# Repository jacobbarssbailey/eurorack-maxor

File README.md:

# MaxOr

There are a number of commercial eurorack-format synthesizer modules available that will work as a logical OR function. While they do a fine job combining multiple gate/trigger signals, typically they work by passing each input through a diode, resulting in the output being the maximum input level minus the the voltage drop across the diodes. Fine for gates and triggers, not so fine for combining control voltages.

This module takes a similar approach to these passive modules, but exchanges the passive diodes for "ideal" diodes (i.e. an opamp and two diodes that conspire to behave like normal diodes, only with a magical 0V voltage drop). The result is a module that precisely combines multiple CVs, and outputs the maximum value from the set.

### Why would you want this?

* Combine several envelopes in a new way
* Combine gate / trigger signals without losing 1V-2V in the process
* Use a constant voltage source to set a lower bound on another CV
* Something else!

## Behavior

Each channel accepts three inputs, and the maximum (positive) voltage among them becomes the output. Some examples of what you should expect:

| Input A | Input B | Input C | Output |
| ------- | ------- | ------- | ------ |
|      0V |      0V |      1V |     1V |
|      1V |      3V |      2V |     3V |
|      5V |      0V |      5V |     5V |
|      5V |      8V |      5V |     8V |
|     -5V |     -8V |      0V |     0V |
|     -8V |     -3V |     -2V |     0V |

Note that this module does nothing for negative voltages; they are treated as if they were 0V. For this reason alone, I don't recommend using this module for audio signals.

## Construction

This module is designed to be milled from a single singled PCB, on an Othermill, though it should also be relatively easy to etch by hand. As such, I've favored hand-solderable surface mount components, to limit the amount of through-hole drilling, and kept all trace gaps to no less than 1/64". The board design could probably be better optimized, before being sent to a commercial board manufacturer, but for home milling, it works quite well.

Jacks are Erthenvar horizontal jacks. At time of writing, they come in packs of 50, and have nice heavy solder tabs.

Pads for protection diodes are included, but to use these, you'll need to cut /remove the traces across them. I included them and then didn't bother with them, in favor of a keyed power connector.

There are no extra power smoothing capacitors on this module, just some 100nF decoupling capacitors around the op amps. If your power distribution board doesn't already contain a few 100µF capacitors nearby, you might find this module oscillating.

Total module depth is about 1.7" (~44mm).

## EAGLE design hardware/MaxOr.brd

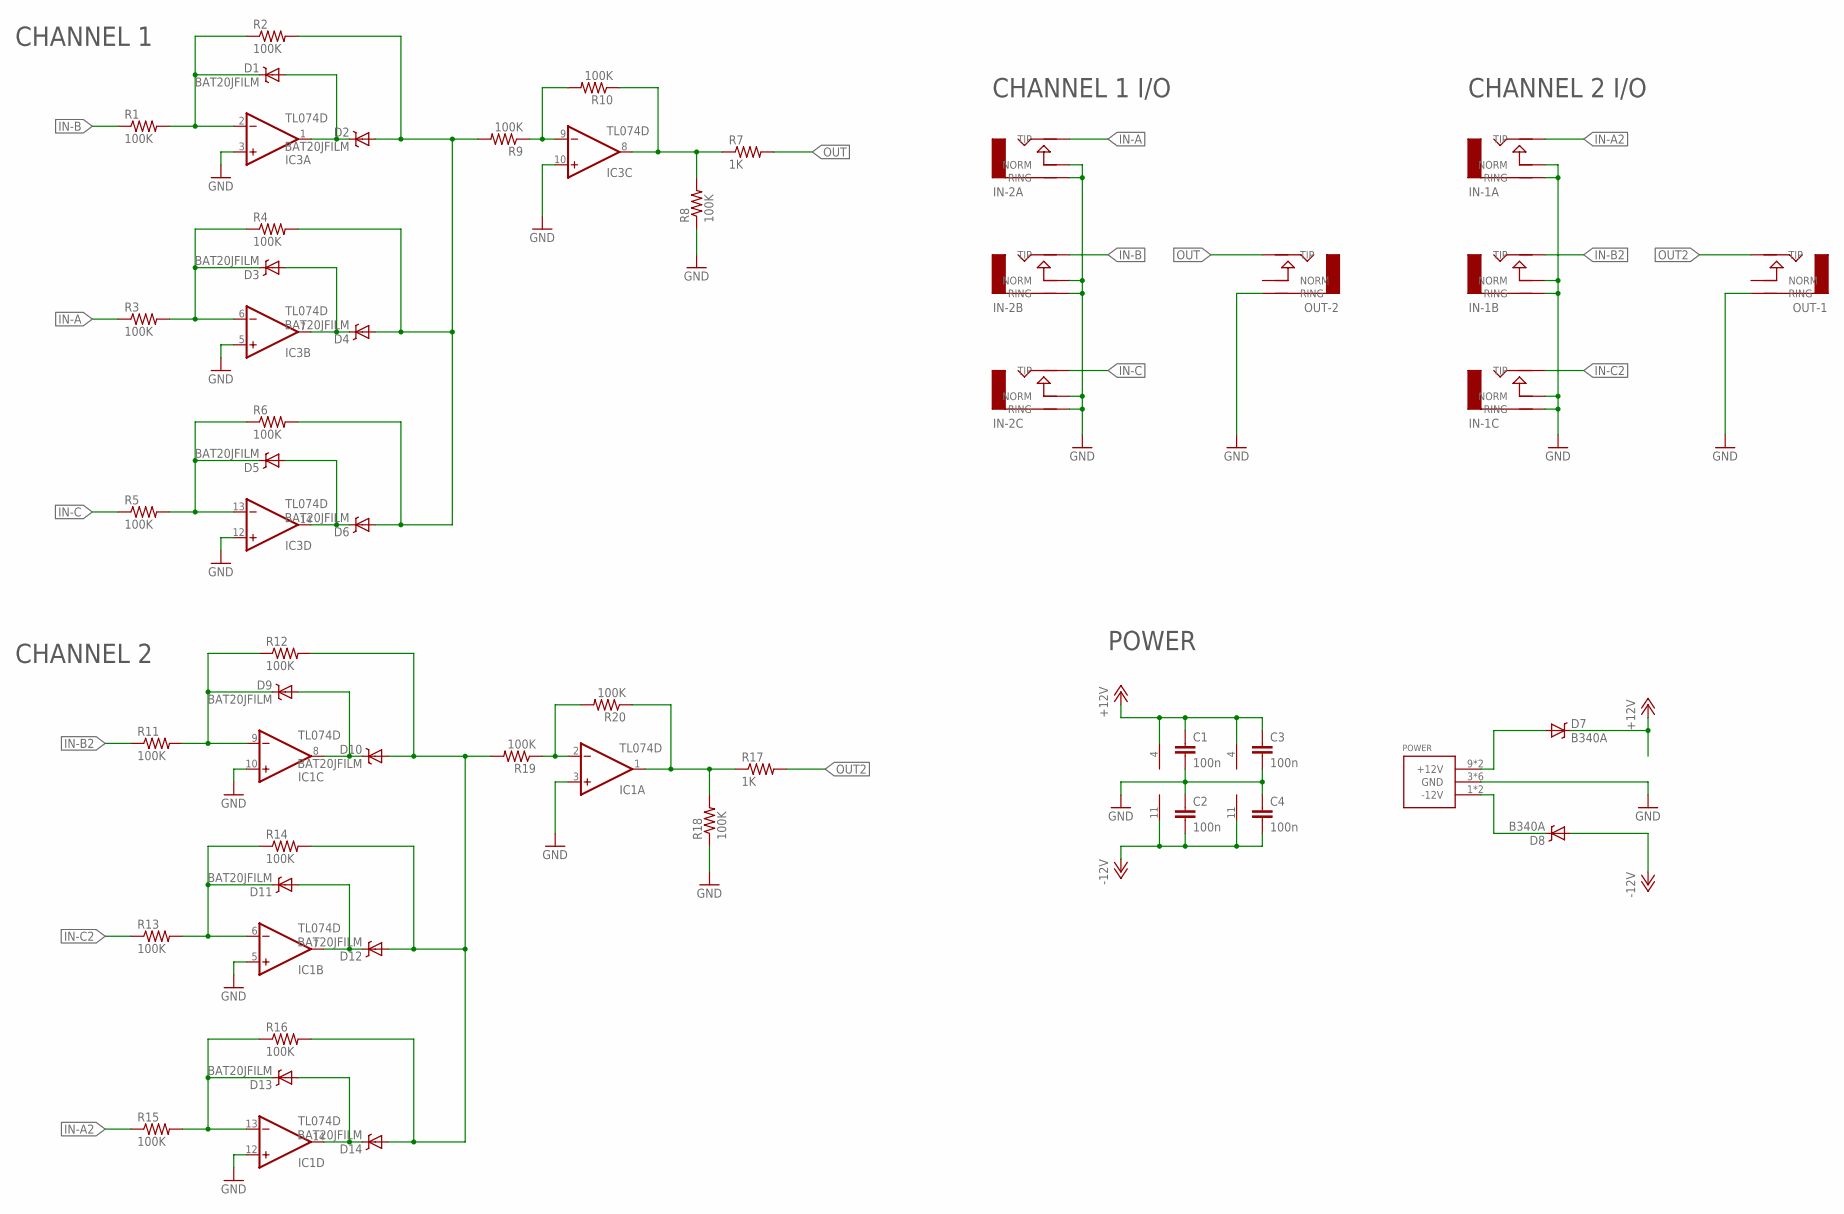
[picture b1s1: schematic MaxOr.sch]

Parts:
C1, C2, C3, C4: 100n; 0805
D1, D2, D3, D4, D5, D6, D9, D10, D11, D12, D13, D14: BAT20JFILM; SOD-323
D7, D8: B340A; SMA-DIODE
IC1, IC3: TL074D; SO14
IN-1A, IN-1B, IN-1C, IN-2A, IN-2B, IN-2C: AUDIO-JACK; ERTHENVAR-JACK-HORIZONTAL
OUT-1, OUT-2: AUDIO-JACK; ERTHENVAR-JACK-HORIZONTAL
POWER: POWER_SIMPLE10; POWER_10
R1, R2, R3, R4, R5, R6, R8, R9, R10, R11, R12, R13, R14, R15, R16, R18, R19, R20: 100K; 0805
R7, R17: 1K; 0805

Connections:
+12V: C1.1, C3.1, D7.C, IC1.4 (V+), IC3.4 (V+)
-12V: C2.2, C4.2, D8.A, IC1.11 (V-), IC3.11 (V-)
BUFFER: IC3.8 (OUT), R7.1, R8.2, R10.1
BUFFER1: IC1.1 (OUT), R17.1, R18.2, R20.1
GND: C1.2, C2.1, C3.2, C4.1, IC1.3 (+IN), IC1.5 (+IN), IC1.10 (+IN), IC1.12 (+IN), IC3.3 (+IN), IC3.5 (+IN), IC3.10 (+IN), IC3.12 (+IN), IN-1A.N (NORM), IN-1A.R@2 (RING), IN-1B.N (NORM), IN-1B.R@2 (RING), IN-1C.N (NORM), IN-1C.R@2 (RING), IN-2A.N (NORM), IN-2A.R@2 (RING), IN-2B.N (NORM), IN-2B.R@2 (RING), IN-2C.N (NORM), IN-2C.R@2 (RING), OUT-1.R@2 (RING), OUT-2.R@2 (RING), POWER.3 (GND), POWER.4 (GND), POWER.5 (GND), POWER.6 (GND), POWER.7 (GND), POWER.8 (GND), R8.1, R18.1
IN-A: IN-2A.T (TIP), R3.1
IN-A2: IN-1A.T (TIP), R15.1
IN-B: IN-2B.T (TIP), R1.1
IN-B2: IN-1B.T (TIP), R11.1
IN-C: IN-2C.T (TIP), R5.1
IN-C2: IN-1C.T (TIP), R13.1
unnamed: D1.A, D2.C, IC3.1 (OUT)
unnamed: D3.A, D4.C, IC3.7 (OUT)
unnamed: D1.C, IC3.2 (-IN), R1.2, R2.1
unnamed: D3.C, IC3.6 (-IN), R3.2, R4.1
unnamed: D5.A, D6.C, IC3.14 (OUT)
unnamed: D5.C, IC3.13 (-IN), R5.2, R6.1
unnamed: D7.A, POWER.9 (+12V), POWER.10 (+12V)
unnamed: D8.C, POWER.1 (-12V), POWER.2 (-12V)
unnamed: IC3.9 (-IN), R9.1, R10.2
unnamed: D9.A, D10.C, IC1.8 (OUT)
unnamed: D9.C, IC1.9 (-IN), R11.2, R12.1
unnamed: D11.A, D12.C, IC1.7 (OUT)
unnamed: D11.C, IC1.6 (-IN), R13.2, R14.1
unnamed: D13.A, D14.C, IC1.14 (OUT)
unnamed: D13.C, IC1.13 (-IN), R15.2, R16.1
unnamed: IC1.2 (-IN), R19.1, R20.2
OUT: OUT-2.T (TIP), R7.2
OUT2: OUT-1.T (TIP), R17.2
PREBUFFERED: D2.A, D4.A, D6.A, R2.2, R4.2, R6.2, R9.2
PREBUFFERED1: D10.A, D12.A, D14.A, R12.2, R14.2, R16.2, R19.2

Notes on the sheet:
CHANNEL 1
CHANNEL 2
CHANNEL 1 I/O
CHANNEL 2 I/O
POWER

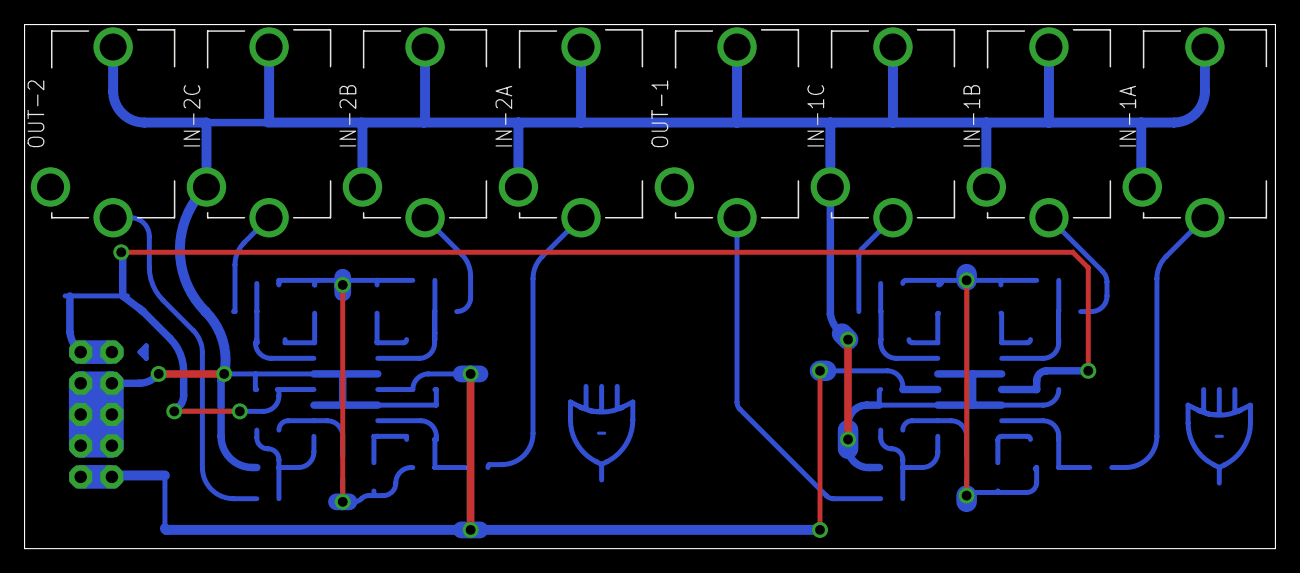
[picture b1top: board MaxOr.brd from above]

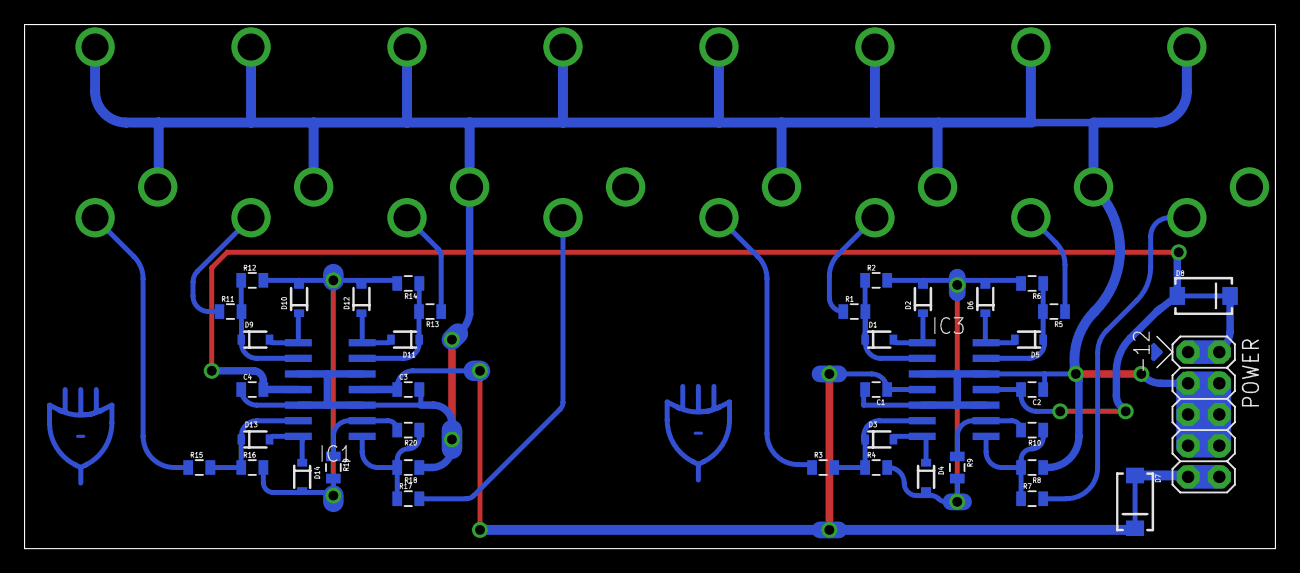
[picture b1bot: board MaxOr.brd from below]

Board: 2 copper layers, 101.9 x 42.7 mm, 49 parts (41 on the bottom side), 31 nets.

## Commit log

2015-08-24 stub readme
2015-08-24 fix missing words
2015-08-24 remainder of readme, still lacking actual design and links
2015-08-24 minor wording changes
2015-08-31 addding eagle files
2015-10-31 example photos, pdf versions, split panel + board

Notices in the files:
parts and their libraries:
SparkFun-DiscreteSemi: Licensing: Creative Commons ShareAlike 4.0 International - https://creativecommons.org/licenses/by-sa/4.0
